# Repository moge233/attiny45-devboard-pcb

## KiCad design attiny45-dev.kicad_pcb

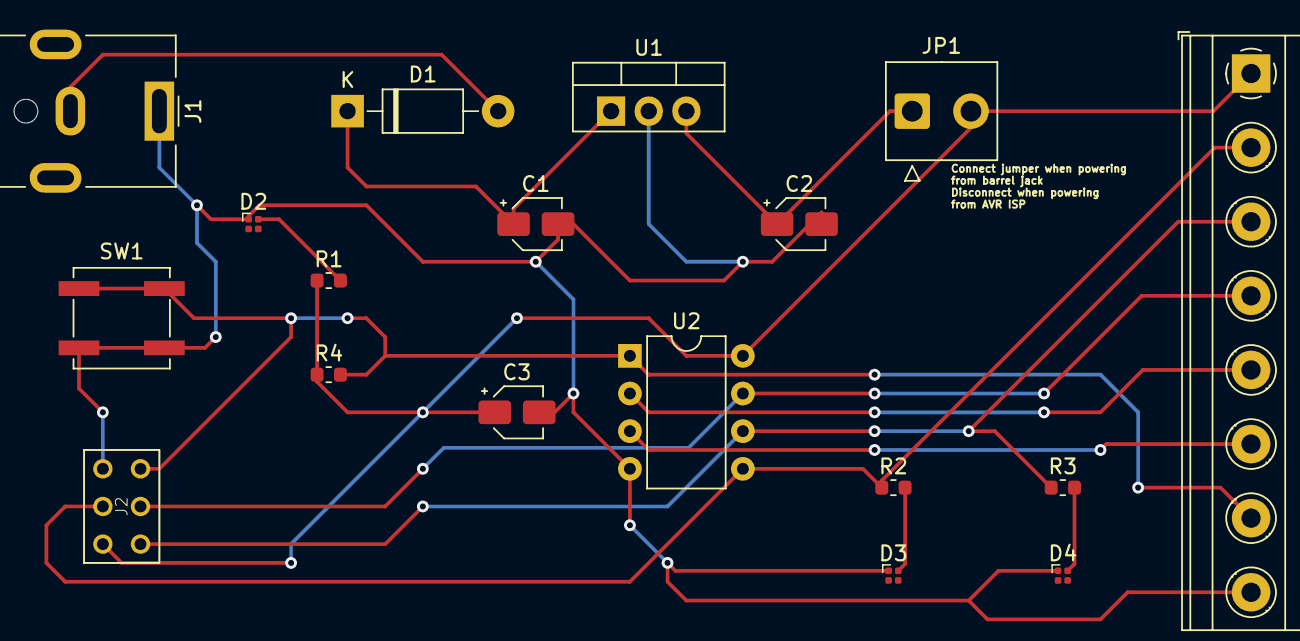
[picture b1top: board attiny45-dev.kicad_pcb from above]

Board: 2 copper layers, 18 parts (0 on the bottom side), 14 nets.

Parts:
C1, C2: 47u; CP_Elec_3x5.4
C3: 0.1u; CP_Elec_3x5.4
D1: 1N4001; D_DO-41_SOD81_P10.16mm_Horizontal
D2, D3, D4: LED; LED_Lumex_SML-LX0303SIUPGUSB
J1: Barrel_Jack; BarrelJack_CUI_PJ-063AH_Horizontal
J2: AVR-ISP-6; AVR-ISP
J3: Screw_Terminal_01x08; TerminalBlock_Phoenix_MKDS-1,5-8_1x08_P5.00mm_Horizontal
JP1: Jumper_2_Open; TE_826576-2_1x02_P3.96mm_Vertical
R1, R2, R3: 500; R_0603_1608Metric
R4: 1000; R_0603_1608Metric
SW1: SW_Push; SW_SPST_B3SL-1022P
U1: LM7805_TO220; TO-220-3_Vertical
U2: ATtiny45-20PU; DIP-8_W7.62mm

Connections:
/PB0: J2.4, J3.2, R2.1, U2.5
/PB1: J2.1, J3.3, R3.1, U2.6
/PB2: J2.3, J3.4, U2.7
/PB3: J3.5, U2.2
/PB4: J3.6, U2.3
/PB5: J2.5, J3.7, R4.2, SW1.1, U2.1
GND: C1.2, C2.2, C3.2, D2.1, D3.1, D4.1, J1.1, J2.6, J3.8, SW1.2, U1.2, U2.4
unnamed: C1.1, D1.1, U1.1
unnamed: C2.1, JP1.1, U1.3
unnamed: D1.2, J1.2
unnamed: D2.2, R1.2
unnamed: D3.2, R2.2
unnamed: D4.2, R3.2
VCC: C3.1, J2.2, J3.1, JP1.2, R1.1, R4.1, U2.8

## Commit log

2020-06-21 Upload screenshots
